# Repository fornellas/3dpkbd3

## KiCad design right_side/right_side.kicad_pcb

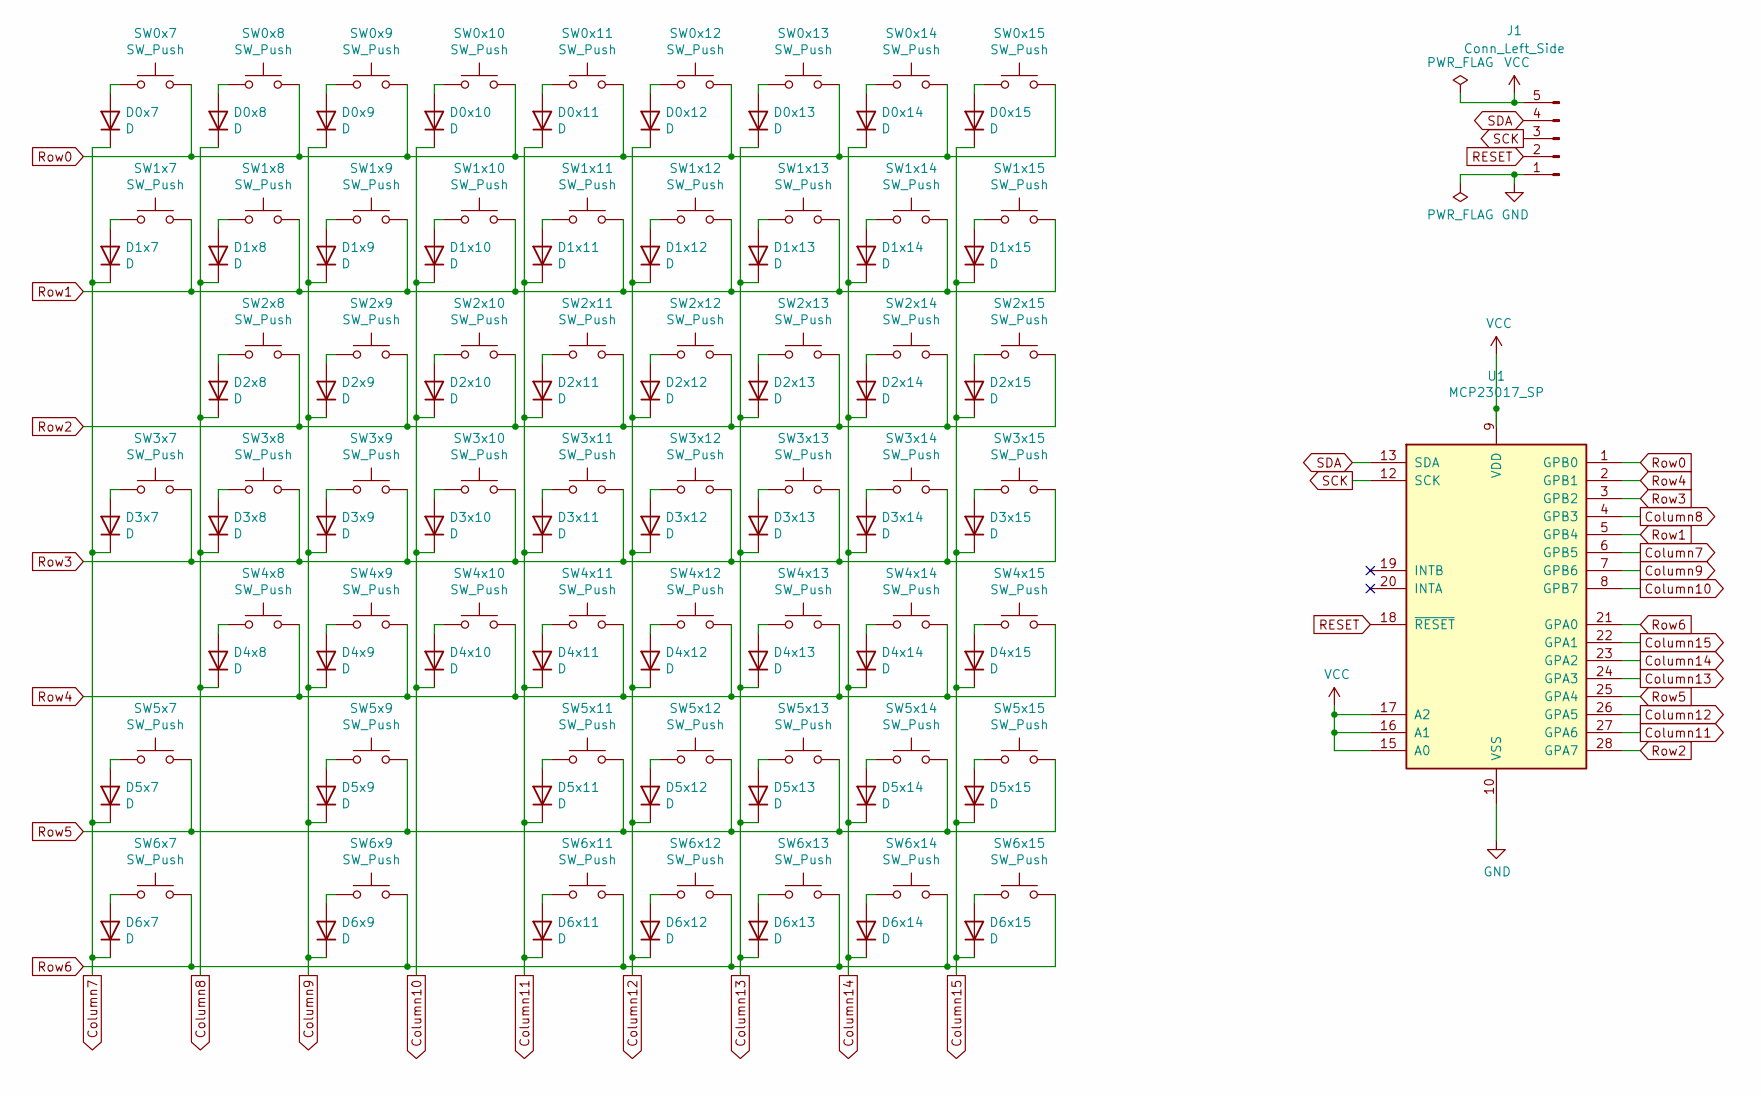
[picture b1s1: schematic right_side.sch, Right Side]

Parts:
D0x7, D0x8, D0x9, D0x10, D0x11, D0x12, D0x13, D0x14, D0x15, D1x7, D1x8, D1x9, D1x10, D1x11, D1x12, D1x13, D1x14, D1x15, D2x8, D2x9, D2x10, D2x11, D2x12, D2x13, D2x14, D2x15, D3x7, D3x8, D3x9, D3x10, D3x11, D3x12, D3x13, D3x14, D3x15, D4x8, D4x9, D4x10, D4x11, D4x12, D4x13, D4x14, D4x15, D5x7, D5x9, D5x11, D5x12, D5x13, D5x14, D5x15, D6x7, D6x9, D6x11, D6x12, D6x13, D6x14, D6x15: D; D_DO-35_SOD27_P7.62mm_Horizontal
J1: Conn_Left_Side; PinHeader_1x05_P2.54mm_Vertical
SW0x7, SW0x8, SW0x9, SW0x10, SW0x11, SW0x12, SW0x13, SW0x14, SW0x15, SW1x7, SW1x8, SW1x9, SW1x10, SW1x11, SW1x12, SW1x13, SW1x14, SW1x15, SW2x8, SW2x9, SW2x10, SW2x11, SW2x12, SW2x13, SW2x14, SW2x15, SW3x7, SW3x8, SW3x9, SW3x10, SW3x11, SW3x12, SW3x13, SW3x14, SW3x15, SW4x8, SW4x9, SW4x10, SW4x11, SW4x12, SW4x13, SW4x14, SW4x15, SW5x7, SW5x9, SW5x11, SW5x12, SW5x13, SW5x14, SW5x15, SW6x7, SW6x9, SW6x11, SW6x12, SW6x13, SW6x14, SW6x15: SW_Push; SW_Cherry_MX_Plate_Kailh_PCB_Socket
U1: MCP23017_SP; DIP-28_W7.62mm_Socket

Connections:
Column7: D0x7.1 (K), D1x7.1 (K), D3x7.1 (K), D5x7.1 (K), D6x7.1 (K), U1.6 (GPB5)
Column8: D0x8.1 (K), D1x8.1 (K), D2x8.1 (K), D3x8.1 (K), D4x8.1 (K), U1.4 (GPB3)
Column9: D0x9.1 (K), D1x9.1 (K), D2x9.1 (K), D3x9.1 (K), D4x9.1 (K), D5x9.1 (K), D6x9.1 (K), U1.7 (GPB6)
Column10: D0x10.1 (K), D1x10.1 (K), D2x10.1 (K), D3x10.1 (K), D4x10.1 (K), U1.8 (GPB7)
Column11: D0x11.1 (K), D1x11.1 (K), D2x11.1 (K), D3x11.1 (K), D4x11.1 (K), D5x11.1 (K), D6x11.1 (K), U1.27 (GPA6)
Column12: D0x12.1 (K), D1x12.1 (K), D2x12.1 (K), D3x12.1 (K), D4x12.1 (K), D5x12.1 (K), D6x12.1 (K), U1.26 (GPA5)
Column13: D0x13.1 (K), D1x13.1 (K), D2x13.1 (K), D3x13.1 (K), D4x13.1 (K), D5x13.1 (K), D6x13.1 (K), U1.24 (GPA3)
Column14: D0x14.1 (K), D1x14.1 (K), D2x14.1 (K), D3x14.1 (K), D4x14.1 (K), D5x14.1 (K), D6x14.1 (K), U1.23 (GPA2)
Column15: D0x15.1 (K), D1x15.1 (K), D2x15.1 (K), D3x15.1 (K), D4x15.1 (K), D5x15.1 (K), D6x15.1 (K), U1.22 (GPA1)
GND: J1.1, U1.10 (VSS)
unnamed: D0x7.2 (A), SW0x7.1
unnamed: D0x8.2 (A), SW0x8.1
unnamed: D0x9.2 (A), SW0x9.1
unnamed: D0x10.2 (A), SW0x10.1
unnamed: D0x11.2 (A), SW0x11.1
unnamed: D0x12.2 (A), SW0x12.1
unnamed: D0x13.2 (A), SW0x13.1
unnamed: D0x14.2 (A), SW0x14.1
unnamed: D0x15.2 (A), SW0x15.1
unnamed: D1x7.2 (A), SW1x7.1
unnamed: D1x8.2 (A), SW1x8.1
unnamed: D1x9.2 (A), SW1x9.1
unnamed: D1x10.2 (A), SW1x10.1
unnamed: D1x11.2 (A), SW1x11.1
unnamed: D1x12.2 (A), SW1x12.1
unnamed: D1x13.2 (A), SW1x13.1
unnamed: D1x14.2 (A), SW1x14.1
unnamed: D1x15.2 (A), SW1x15.1
unnamed: D2x8.2 (A), SW2x8.1
unnamed: D2x9.2 (A), SW2x9.1
unnamed: D2x10.2 (A), SW2x10.1
unnamed: D2x11.2 (A), SW2x11.1
unnamed: D2x12.2 (A), SW2x12.1
unnamed: D2x13.2 (A), SW2x13.1
unnamed: D2x14.2 (A), SW2x14.1
unnamed: D2x15.2 (A), SW2x15.1
unnamed: D3x7.2 (A), SW3x7.1
unnamed: D3x8.2 (A), SW3x8.1
unnamed: D3x9.2 (A), SW3x9.1
unnamed: D3x10.2 (A), SW3x10.1
unnamed: D3x11.2 (A), SW3x11.1
unnamed: D3x12.2 (A), SW3x12.1
unnamed: D3x13.2 (A), SW3x13.1
unnamed: D3x14.2 (A), SW3x14.1
unnamed: D3x15.2 (A), SW3x15.1
unnamed: D4x8.2 (A), SW4x8.1
unnamed: D4x9.2 (A), SW4x9.1
unnamed: D4x10.2 (A), SW4x10.1
unnamed: D4x11.2 (A), SW4x11.1
unnamed: D4x12.2 (A), SW4x12.1
unnamed: D4x13.2 (A), SW4x13.1
unnamed: D4x14.2 (A), SW4x14.1
unnamed: D4x15.2 (A), SW4x15.1
unnamed: D5x7.2 (A), SW5x7.1
unnamed: D5x9.2 (A), SW5x9.1
unnamed: D5x11.2 (A), SW5x11.1
unnamed: D5x12.2 (A), SW5x12.1
unnamed: D5x13.2 (A), SW5x13.1
unnamed: D5x14.2 (A), SW5x14.1
unnamed: D5x15.2 (A), SW5x15.1
unnamed: D6x7.2 (A), SW6x7.1
unnamed: D6x9.2 (A), SW6x9.1
unnamed: D6x11.2 (A), SW6x11.1
unnamed: D6x12.2 (A), SW6x12.1
unnamed: D6x13.2 (A), SW6x13.1
unnamed: D6x14.2 (A), SW6x14.1
unnamed: D6x15.2 (A), SW6x15.1
RESET: J1.2, U1.18 (~RESET~)
Row0: SW0x7.2, SW0x8.2, SW0x9.2, SW0x10.2, SW0x11.2, SW0x12.2, SW0x13.2, SW0x14.2, SW0x15.2, U1.1 (GPB0)
Row1: SW1x7.2, SW1x8.2, SW1x9.2, SW1x10.2, SW1x11.2, SW1x12.2, SW1x13.2, SW1x14.2, SW1x15.2, U1.5 (GPB4)
Row2: SW2x8.2, SW2x9.2, SW2x10.2, SW2x11.2, SW2x12.2, SW2x13.2, SW2x14.2, SW2x15.2, U1.28 (GPA7)
Row3: SW3x7.2, SW3x8.2, SW3x9.2, SW3x10.2, SW3x11.2, SW3x12.2, SW3x13.2, SW3x14.2, SW3x15.2, U1.3 (GPB2)
Row4: SW4x8.2, SW4x9.2, SW4x10.2, SW4x11.2, SW4x12.2, SW4x13.2, SW4x14.2, SW4x15.2, U1.2 (GPB1)
Row5: SW5x7.2, SW5x9.2, SW5x11.2, SW5x12.2, SW5x13.2, SW5x14.2, SW5x15.2, U1.25 (GPA4)
Row6: SW6x7.2, SW6x9.2, SW6x11.2, SW6x12.2, SW6x13.2, SW6x14.2, SW6x15.2, U1.21 (GPA0)
SCK: J1.3, U1.12 (SCK)
SDA: J1.4, U1.13 (SDA)
VCC: J1.5, U1.9 (VDD), U1.15 (A0), U1.16 (A1), U1.17 (A2)

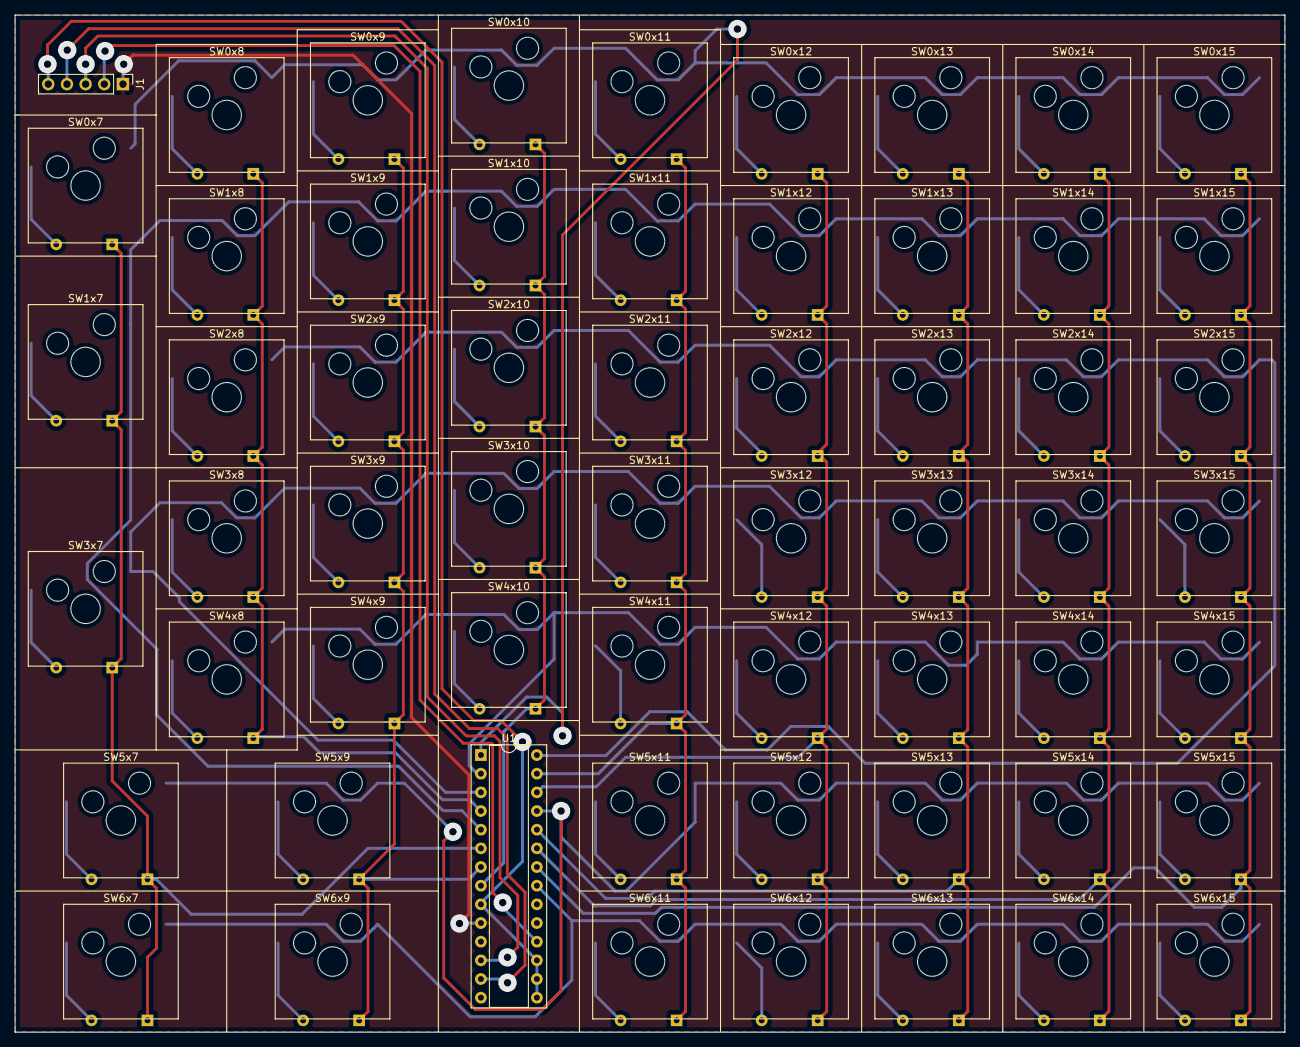
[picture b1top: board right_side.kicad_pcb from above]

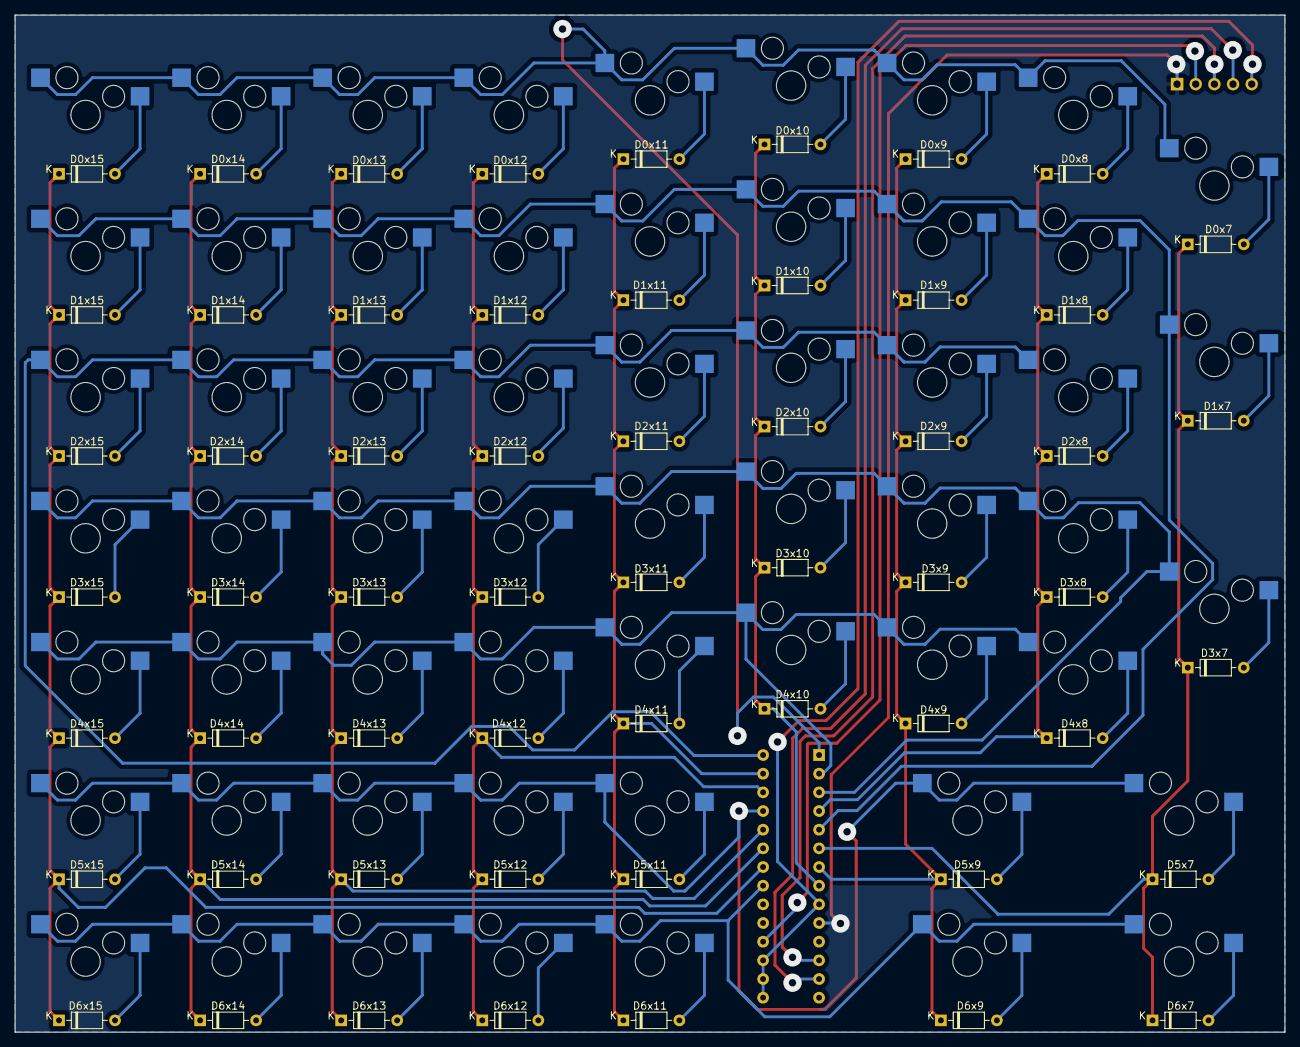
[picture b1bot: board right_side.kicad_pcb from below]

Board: 2 copper layers, 172.8 x 138.4 mm, 116 parts (57 on the bottom side), 78 nets.

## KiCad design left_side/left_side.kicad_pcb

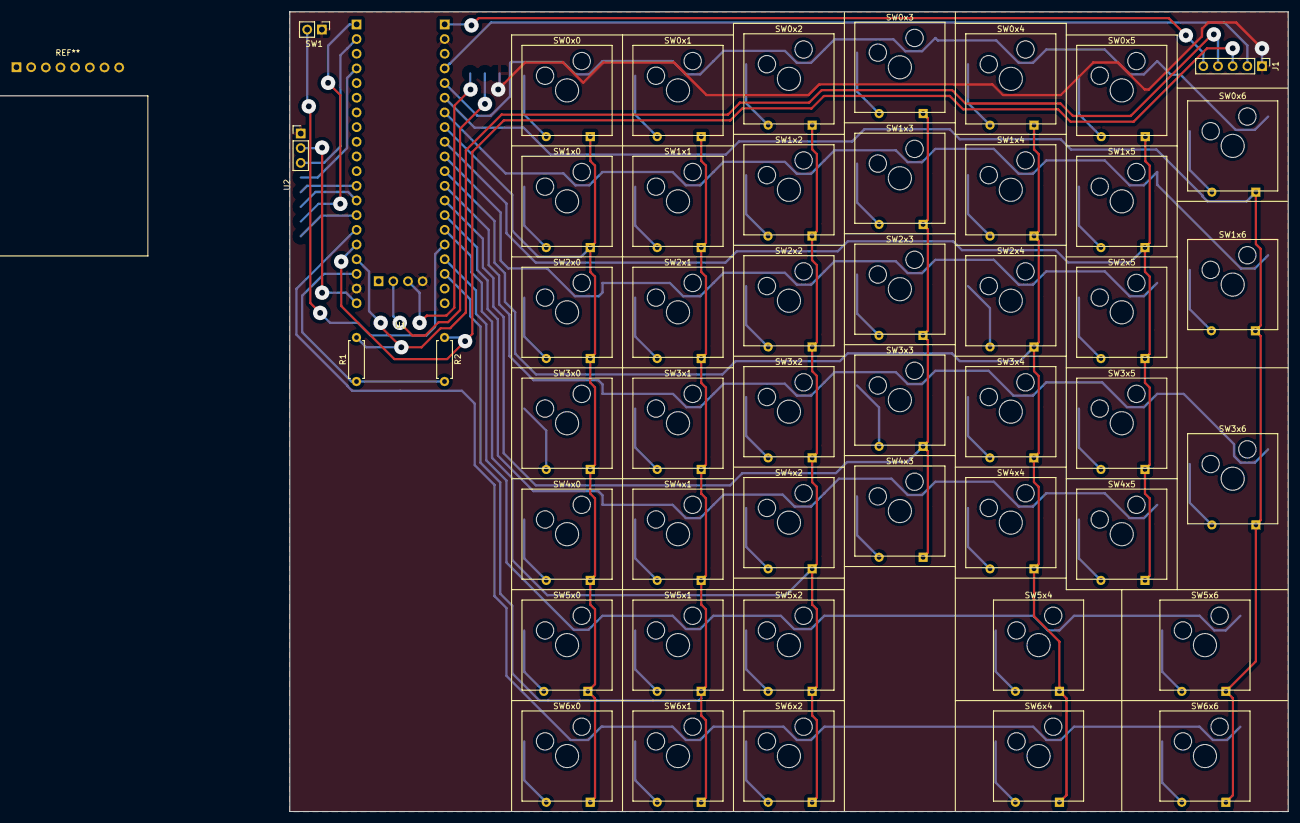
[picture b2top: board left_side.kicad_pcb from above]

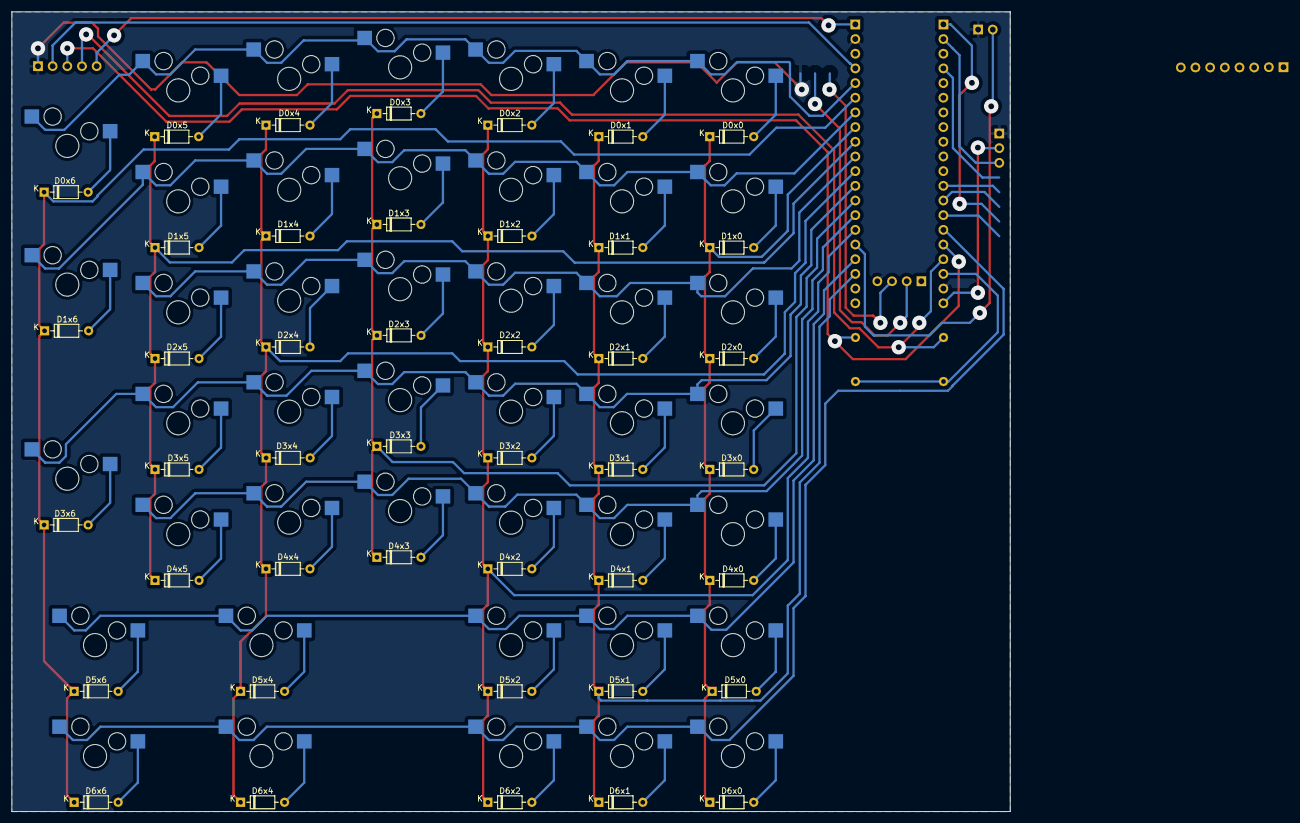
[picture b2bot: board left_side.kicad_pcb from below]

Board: 2 copper layers, 172.8 x 138.4 mm, 92 parts (43 on the bottom side), 66 nets.

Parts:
D0x0, D0x1, D0x2, D0x3, D0x4, D0x5, D0x6, D1x0, D1x1, D1x2, D1x3, D1x4, D1x5, D1x6, D2x0, D2x1, D2x2, D2x3, D2x4, D2x5, D3x0, D3x1, D3x2, D3x3, D3x4, D3x5, D3x6, D4x0, D4x1, D4x2, D4x3, D4x4, D4x5, D5x0, D5x1, D5x2, D5x4, D5x6, D6x0, D6x1, D6x2, D6x4, D6x6: D; D_DO-35_SOD27_P7.62mm_Horizontal
J1: Conn_Right_Side; PinHeader_1x05_P2.54mm_Vertical
R1, R2: 4k7; R_Axial_DIN0207_L6.3mm_D2.5mm_P7.62mm_Horizontal
SW0x0, SW0x1, SW0x2, SW0x3, SW0x4, SW0x5, SW0x6, SW1x0, SW1x1, SW1x2, SW1x3, SW1x4, SW1x5, SW1x6, SW2x0, SW2x1, SW2x2, SW2x3, SW2x4, SW2x5, SW3x0, SW3x1, SW3x2, SW3x3, SW3x4, SW3x5, SW3x6, SW4x0, SW4x1, SW4x2, SW4x3, SW4x4, SW4x5, SW5x0, SW5x1, SW5x2, SW5x4, SW5x6, SW6x0, SW6x1, SW6x2, SW6x4, SW6x6: SW_Push; SW_Cherry_MX_Plate_Kailh_PCB_Socket
SW1: SW_NRST; PinHeader_1x02_P2.54mm_Vertical
U1: STM32F411CEU6_Core_Board
U2: ST77891.5; PinHeader_1x08_P2.54mm_Vertical

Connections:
+3V3: U1.20, U1.21, U1.42
+5V: J1.5, R1.1, R2.1, U1.18, U1.44
Column0: D0x0.1, D1x0.1, D2x0.1, D3x0.1, D4x0.1, D5x0.1, D6x0.1, U1.37
Column1: D0x1.1, D1x1.1, D2x1.1, D3x1.1, D4x1.1, D5x1.1, D6x1.1, U1.27
Column2: D0x2.1, D1x2.1, D2x2.1, D3x2.1, D4x2.1, D5x2.1, D6x2.1, U1.30
Column3: D0x3.1, D1x3.1, D2x3.1, D3x3.1, D4x3.1, U1.32
Column4: D0x4.1, D1x4.1, D2x4.1, D3x4.1, D4x4.1, D5x4.1, D6x4.1, U1.34
Column5: D0x5.1, D1x5.1, D2x5.1, D3x5.1, D4x5.1, U1.36
Column6: D0x6.1, D1x6.1, D3x6.1, D5x6.1, D6x6.1, U1.39
GND: J1.1, SW1.1, U1.19, U1.24, U1.43, U2.1
I2C1_SCL: J1.3, R2.2, U1.16
I2C1_SDA: J1.4, R1.2, U1.17
MCP2307_RESET: J1.2, U1.41
NRST: SW1.2, U1.29
unnamed: D0x0.2, SW0x0.1
unnamed: D0x1.2, SW0x1.1
unnamed: D0x2.2, SW0x2.1
unnamed: D0x3.2, SW0x3.1
unnamed: D0x4.2, SW0x4.1
unnamed: D0x5.2, SW0x5.1
unnamed: D0x6.2, SW0x6.1
unnamed: D1x0.2, SW1x0.1
unnamed: D1x1.2, SW1x1.1
unnamed: D1x2.2, SW1x2.1
unnamed: D1x3.2, SW1x3.1
unnamed: D1x4.2, SW1x4.1
unnamed: D1x5.2, SW1x5.1
unnamed: D1x6.2, SW1x6.1
unnamed: D2x0.2, SW2x0.1
unnamed: D2x1.2, SW2x1.1
unnamed: D2x2.2, SW2x2.1
unnamed: D2x3.2, SW2x3.1
unnamed: D2x4.2, SW2x4.1
unnamed: D2x5.2, SW2x5.1
unnamed: D3x0.2, SW3x0.1
unnamed: D3x1.2, SW3x1.1
unnamed: D3x2.2, SW3x2.1
unnamed: D3x3.2, SW3x3.1
unnamed: D3x4.2, SW3x4.1
unnamed: D3x5.2, SW3x5.1
unnamed: D3x6.2, SW3x6.1
unnamed: D4x0.2, SW4x0.1
unnamed: D4x1.2, SW4x1.1
unnamed: D4x2.2, SW4x2.1
unnamed: D4x3.2, SW4x3.1
unnamed: D4x4.2, SW4x4.1
unnamed: D4x5.2, SW4x5.1
unnamed: D5x0.2, SW5x0.1
unnamed: D5x1.2, SW5x1.1
unnamed: D5x2.2, SW5x2.1
unnamed: D5x4.2, SW5x4.1
unnamed: D5x6.2, SW5x6.1
unnamed: D6x0.2, SW6x0.1
unnamed: D6x1.2, SW6x1.1
unnamed: D6x2.2, SW6x2.1
unnamed: D6x4.2, SW6x4.1
unnamed: D6x6.2, SW6x6.1
Row0: SW0x0.2, SW0x1.2, SW0x2.2, SW0x3.2, SW0x4.2, SW0x5.2, SW0x6.2, U1.40
Row1: SW1x0.2, SW1x1.2, SW1x2.2, SW1x3.2, SW1x4.2, SW1x5.2, SW1x6.2, U1.38
Row2: SW2x0.2, SW2x1.2, SW2x2.2, SW2x3.2, SW2x4.2, SW2x5.2, U1.35
Row3: SW3x0.2, SW3x1.2, SW3x2.2, SW3x3.2, SW3x4.2, SW3x5.2, SW3x6.2, U1.33
Row4: SW4x0.2, SW4x1.2, SW4x2.2, SW4x3.2, SW4x4.2, SW4x5.2, U1.31
Row5: SW5x0.2, SW5x1.2, SW5x2.2, SW5x4.2, SW5x6.2, U1.28
Row6: SW6x0.2, SW6x1.2, SW6x2.2, SW6x4.2, SW6x6.2, U1.15
SWCLK: U1.23, U2.3
SWDIO: U1.22, U2.2

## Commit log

2021-08-14 First public commit
